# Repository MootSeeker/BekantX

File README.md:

<div align="center">

# BekantX

**An open replacement controller for the IKEA BEKANT standing desk, with its schematic, PCB layout and enclosure designed by an AI (Claude) under human review.**

</div>

---

## What this is

BekantX replaces the button box of an IKEA BEKANT sit/stand desk with a custom controller. It provides memory
positions, limits, obstruction detection, a small OLED display, and an optional Wi-Fi link to Home Assistant
that works locally, without a cloud.

The project is also an **experiment**: how far can an AI model take real hardware design? The schematic changes,
the component placement, the 6-layer PCB layout, the parametric 3D-printed enclosure and the fit checks between
board and case were done by [Claude](https://www.anthropic.com/claude) through
[Claude Code](https://claude.com/claude-code). It worked with scripts and the KiCad and build123d APIs, not
through a GUI. A human set the requirements, made the decisions, reviewed every pull request, and printed and
tested the parts.

> [!NOTE]
> Part of the point is to be honest about the results. Every pull request lists what was verified (ERC, DRC,
> fit check, renders) and what was not. Open findings are tracked in the project notes in
> [`Vault/`](Vault/00%20Index.md).

## Highlights

- **Dual controller, safety first.** An STM32G0B1 owns the LIN bus to the desk, motion and every safety rule.
  An optional ESP32-C3 adds Wi-Fi, MQTT and Home Assistant discovery. The desk keeps working without the ESP,
  and the ESP can never move the desk without the STM32's validation.
- **One 6-layer board.** 129 × 38 mm, one track direction per layer: F.Cu vertical, In1 (+3V3 and VCC area),
  In2 horizontal, In3 vertical, In4 (solid GND), B.Cu horizontal. Routed with Freerouting, tuned by parameter
  sweeps, then finished by scripts: tracks through pad and via centres, only 45° corners, via teardrops, short
  supply stubs to the planes and large GND pours on the outer layers that are cut as little as possible.
- **Parametric enclosure.** Built in [build123d](https://github.com/gumyr/build123d), with every dimension a
  named parameter. The board outline, mounting holes, buttons and display position are exported from the
  enclosure model to the PCB (`CAD/board_interface.json`), and the board STEP is checked against the case for
  collisions.
- **Local smart home.** ESP-IDF C++ firmware with a Wi-Fi captive portal, MQTT, Home Assistant auto discovery
  and a status LED.
- **Reproducible.** Every layout step is a script in [`tools/pcb/`](tools/pcb). The design rules, decisions
  and open points are documented in the vault.

## Gallery

<table>
  <tr>
    <td align="center"><br><sub>Front side: six buttons, OLED connector, status LEDs, title block with QR code</sub></td>
    <td align="center"><br><sub>Back side: input protection and regulators, STM32G0B1, ESP32-C3 with chip antenna, USB-C</sub></td>
  </tr>
  <tr>
    <td align="center"><br><sub>Board, case and lid (render of the CAD models)</sub></td>
    <td align="center"><br><sub>Enclosure r3, printed in PLA (without keypad and board)</sub></td>
  </tr>
</table>

## Architecture

```mermaid
flowchart TB
    desk["IKEA BEKANT motor controller"]
    ha["Home Assistant"]
    subgraph board["BekantX controller board"]
        direction TB
        esp["ESP32-C3 (secondary, optional)<br/>Wi-Fi, MQTT"]
        stm["STM32G0B1 (primary)<br/>LIN, motion, limits, safety, memory"]
        hmi["6 buttons, 1.29 in OLED, LEDs"]
    end
    ha <-- "MQTT + discovery" --> esp
    esp <-- "SPI mailbox, validated by the primary" --> stm
    hmi --- stm
    stm <-- "LIN (TLIN1027)" --> desk
```

| Document | Content |
| --- | --- |
| [Requirements](Docs/description.md) | Goals, functional and safety requirements (SR-001 … SR-007) |
| [Architecture](Docs/architecture.md) | Controller split, responsibilities, state ownership |
| [Inter-controller protocol](Docs/inter-controller-protocol.md) | SPI frames between ESP32-C3 and STM32 |
| [BEKANT LIN protocol](Docs/bekant-lin-protocol.md) | What is known about the desk's LIN bus |
| [Assembly guide](Docs/Montageanleitung.md) | Printing, keypad, display, board, lid and mounting under the desktop (German); English PDF: [BekantX_Assembly_Guide.pdf](Docs/BekantX_Assembly_Guide.pdf) |
| [Bill of materials](Docs/BekantX_Bill_of_Materials.pdf) | 127 board placements (6 not populated) and the parts outside the PCB |
| [Renderings and photos](Docs/bilder/README.md) | Board and enclosure renders, photos of the printed case |
| [`Docs/datasheets/`](Docs/datasheets) | Third-party datasheets (display, ESP32, LMR51610), see [LICENSES](LICENSES/README.md) |

## Hardware at a glance

| Block | Parts |
| --- | --- |
| Primary MCU | STM32G0B1KB (QFN-32) |
| Secondary MCU | ESP32-C3 + W25Q32 flash, Johanson 2450AT18A100 chip antenna |
| Desk interface | 3-pin connector (supply, GND, LIN), TLIN1027 LIN transceiver, fuse, TVS SMBJ33CA, reverse-polarity protection |
| Power | LV2862 buck to 12 V (LIN VSUP), LMR51610 buck to 3.3 V, USB-C supply as an alternative |
| USB | USB-C with ESD protection (USBLC6), TS3USB30 switch: USB goes to the ESP32-C3 or to the STM32 |
| User interface | 6 × 6 mm tactile buttons, 1.29" OLED (CH1115) on a 16-pin FPC, SK6812 status LED, RGB LED |
| Board | 6 layers, 1.6 mm (stackup ASSUMPTION, JLC06161H-2116 pattern, not yet checked with the fab), 0.15 / 0.15 mm rules, ENIG |

> [!WARNING]
> The desk's electrical interface (supply voltage, LIN levels, connector pinout) has **not been measured** on a
> real desk yet. Those parts of the design are marked `ASSUMPTION` and listed in
> [`Vault/Offene Punkte.md`](Vault/Offene%20Punkte.md). Do not connect this board to your desk before checking
> them.

## How the AI-driven design works

All the work happens in [Claude Code](https://claude.com/claude-code) against this repository:

- **Project memory**: [`CLAUDE.md`](CLAUDE.md) holds the rules (guardrails for electronics, mechanics, firmware
  and git). The Obsidian vault [`Vault/`](Vault/00%20Index.md) holds the *why*: decisions, status and open
  points. The vault is written in German.
- **Roles as skills**: architecture, schematic design, component selection, PCB design, mechanical CAD,
  firmware, tests, CI and fab export. Each is a skill in [`.claude/skills/`](.claude/skills).
- **Independent review**: read-only reviewer subagents (schematic, PCB, CAD, code) check every change without
  the author's bias. Their findings go into the pull request unchanged.
- **Hooks**: [`.claude/hooks/`](.claude/hooks) enforce the git rules and run ERC/DRC automatically after every
  edit to a KiCad file.
- **Layout pipeline** (KiCad 10 Python API, `pcbnew`):
  1. placement from the enclosure interface;
  2. Freerouting in two stages (power first, then signals), with parameter sweeps;
  3. a custom A* touch-up router;
  4. plane rework, pad-entry straightening and corner chamfering;
  5. supply stubs to the planes, GND pour stitching, the board outline, and the silkscreen with labels, logo and QR code;
  6. the move to 6 layers with one track direction per layer (fan-out, direction-constrained routing runs), 45°
     chamfers instead of 90° corners, via teardrops.

  Details: [`Vault/Toolchain.md`](Vault/Toolchain.md).
- **Mechanics**: [`CAD/src/bekantx_enclosure.py`](CAD/src/bekantx_enclosure.py) builds the case, lid and keypad,
  and exports STEP + STL. [`CAD/src/check_board_fit.py`](CAD/src/check_board_fit.py) checks the real board STEP
  against the case.

## Repository layout

```
CAD/              enclosure exports (STEP/STL), board STEP, board interface; sources in CAD/src
Docs/             requirements, architecture, protocols, assembly guide, bill of materials (PDF)
  bilder/         renderings and photos
  datasheets/     third-party datasheets
Firmware/
  ESP32C3/        ESP-IDF C++ firmware of the secondary controller
  ST/             STM32CubeMX project of the primary controller (no code yet)
Pcb_Controller/   KiCad 10 project: hierarchical schematic and 6-layer board
tools/pcb/        layout pipeline (placement, routing, touch-up, post-processing)
tools/sch/        scripted schematic edits
tools/docs/       PDF builders (bill of materials, assembly guide)
Vault/            project memory (Obsidian, German)
.claude/          skills, reviewer subagents and hooks for Claude Code
```

## Build and check

```bash
# KiCad 10: electrical and design rule checks, 3D export (Windows paths, see Vault/Toolchain.md)
kicad-cli sch erc --format json -o erc.json Pcb_Controller/BekantX.kicad_sch
kicad-cli pcb drc --schematic-parity --format json -o drc.json Pcb_Controller/BekantX.kicad_pcb
kicad-cli pcb export step --subst-models --user-origin 100x80mm -o CAD/BekantX_PCB.step Pcb_Controller/BekantX.kicad_pcb

# Enclosure (Python 3.13 with build123d) and fit check against the board
python CAD/src/bekantx_enclosure.py
python CAD/src/check_board_fit.py

# PDFs: bill of materials (KiCad's Python) and assembly guide (Python with Pillow); both print with Microsoft Edge
"C:/Program Files/KiCad/10.0/bin/python.exe" tools/docs/bom_pdf.py
python tools/docs/makerworld_pdf.py

# ESP32-C3 firmware (ESP-IDF environment)
cd Firmware/ESP32C3/BekantX && idf.py set-target esp32c3 && idf.py build
```

## Status

| Area | State |
| --- | --- |
| Requirements and architecture | done, see `Docs/` |
| Schematic | done; ERC 0 errors (28 old warnings) |
| PCB layout (6 layers) | done and reviewed in KiCad; DRC 0 errors, 0 unconnected, schematic parity OK; not yet manufactured |
| Enclosure r3 | printed (PLA); case and lid fit; fit check against the 6-layer board passes in CAD; final print in PETG pending |
| Bill of materials | 127 placements, 121 to populate; no supplier part numbers yet, J10 and Y1 without MPN |
| Assembly guide | written (German and English PDF); not yet tried with a populated board |
| ESP32-C3 firmware | Wi-Fi provisioning, MQTT, Home Assistant discovery, status LED; developed on an ESP32-S2-Saola board until the controller board exists |
| STM32 firmware | not started (CubeMX pin configuration only) |
| Desk interface | **unverified**: to be measured on a real BEKANT |

The next steps are measuring the desk interface, ordering the first boards, writing the STM32 firmware with the
LIN and motion logic, and the inter-controller SPI link. The full list is in
[`Vault/Offene Punkte.md`](Vault/Offene%20Punkte.md).

## Safety and disclaimer

A standing desk is a heavy, motorised machine. BekantX is a hobby project without any certification. Anything
you build from it is at your own risk. Collision detection is heuristic and is no substitute for paying
attention.
"IKEA" and "BEKANT" are trademarks of Inter IKEA Systems B.V. This project is not affiliated with or endorsed
by IKEA.

## License

| Part | License |
| --- | --- |
| Hardware (`Pcb_Controller/`, `CAD/`) | [CERN-OHL-S-2.0](LICENSE) |
| Software (`Firmware/`, `tools/`, `CAD/src/`, `.claude/`) | [GPL-3.0-or-later](LICENSES/GPL-3.0-or-later.txt) |
| Documentation (`Docs/`, `Vault/`, this README) | [CC-BY-SA-4.0](LICENSES/CC-BY-SA-4.0.txt) |

Details and exceptions (third-party datasheets) are in [`LICENSES/README.md`](LICENSES/README.md).

## Acknowledgements

- [LYFT mk2](https://github.com/mgkoenig/lyft_mk2) by mgkoenig: the idea of a LIN controller plus an ESP for
  the BEKANT.
- [KiCad](https://www.kicad.org/), [Freerouting](https://github.com/freerouting/freerouting),
  [build123d](https://github.com/gumyr/build123d) and [ESP-IDF](https://github.com/espressif/esp-idf).
- Designed with [Claude Code](https://claude.com/claude-code) by Anthropic, reviewed and built by
  [MootSeeker](https://github.com/MootSeeker).

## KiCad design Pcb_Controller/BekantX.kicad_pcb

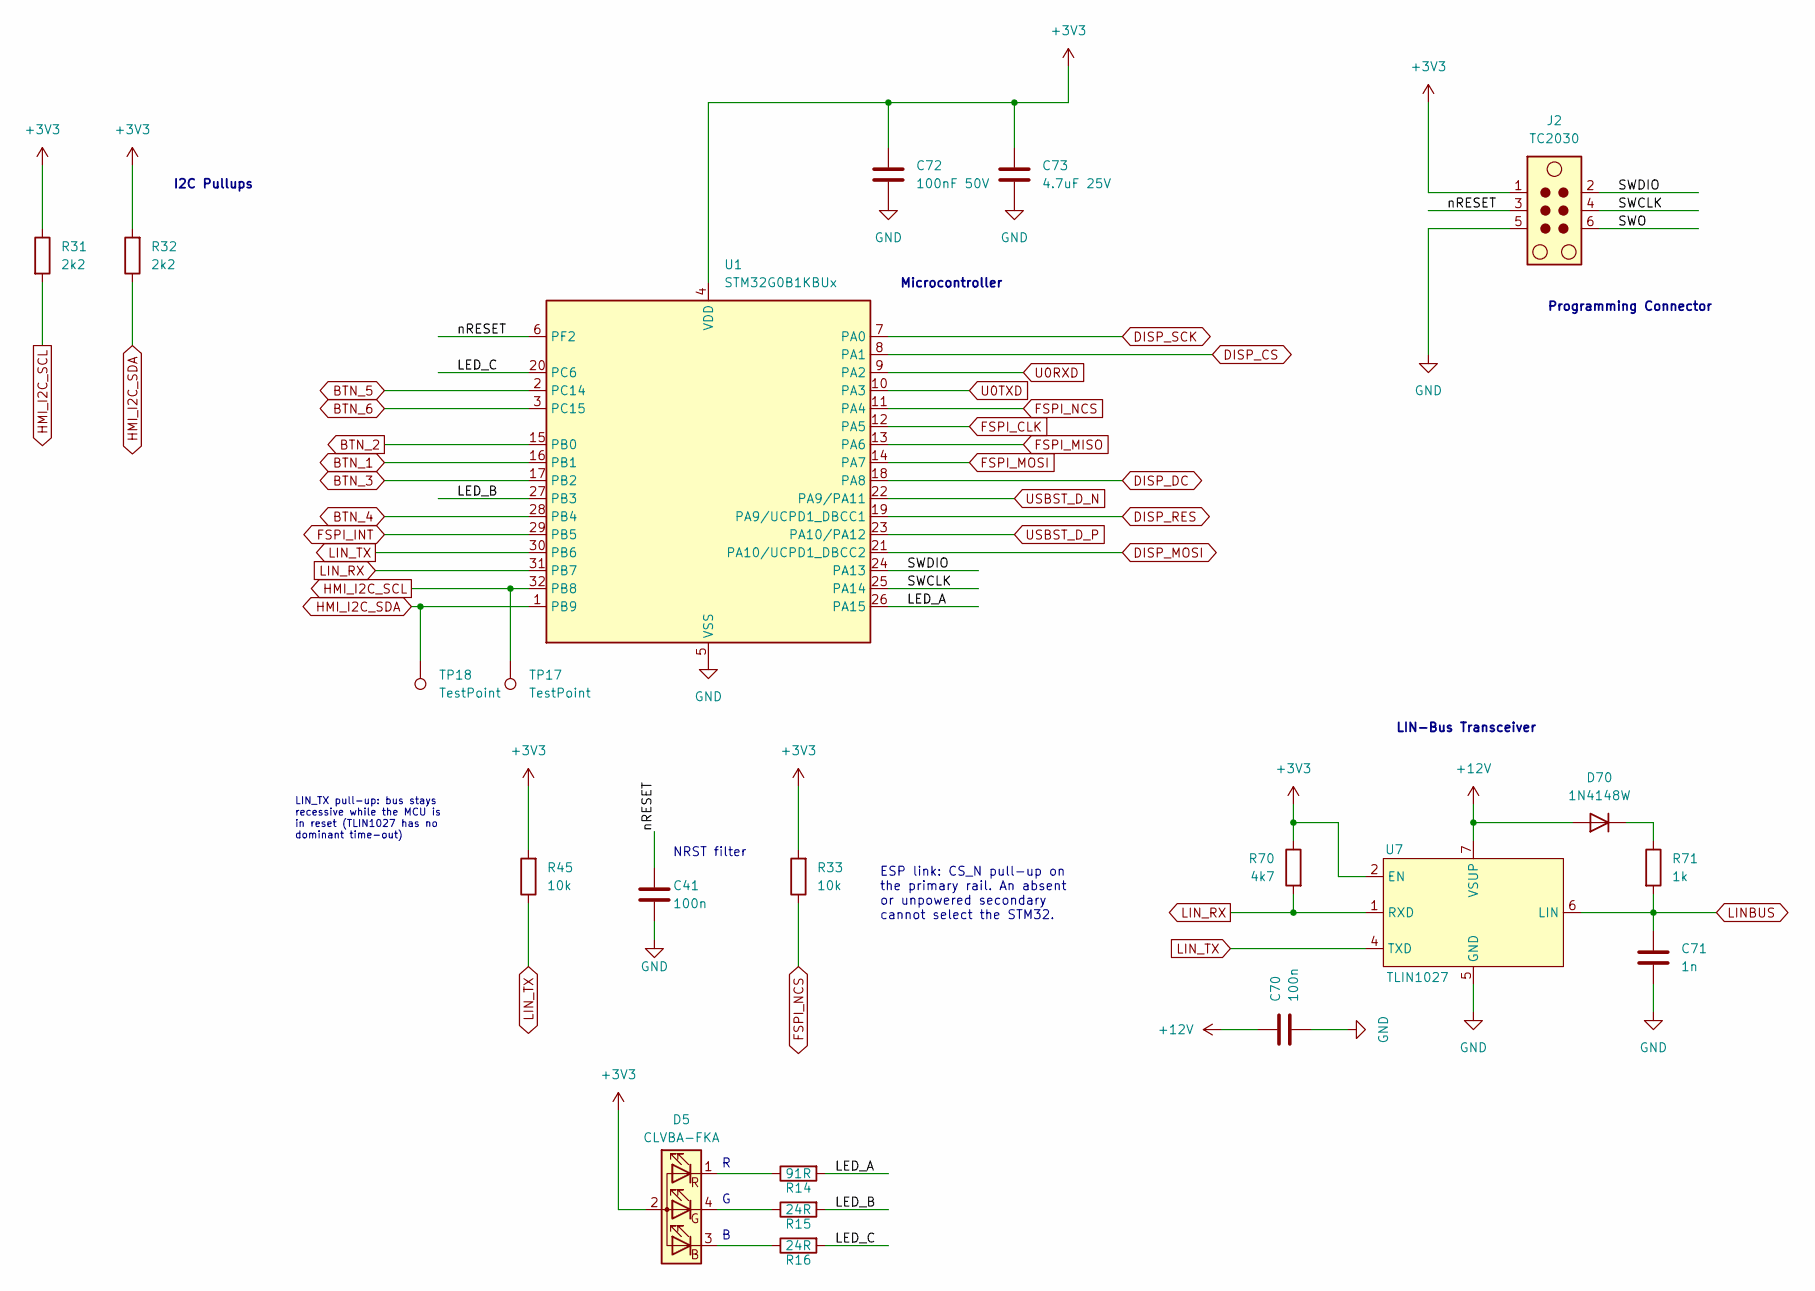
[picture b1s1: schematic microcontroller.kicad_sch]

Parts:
C41, C70: 100n; C_0805_2012Metric; MPN CL21B104KBCNNNC
C71: 1n; C_0805_2012Metric; MPN CL21B102KBANNNC
C72: 100nF 50V; C_0805_2012Metric; MPN CL21B104KBCNNNC
C73: 4.7uF 25V; C_0805_2012Metric; MPN CL21A475KAQNNNE
D5: CLVBA-FKA; LED_Cree-PLCC4_3.2x2.8mm_CCW; MPN CLVBA-FKA-CAEDH8BBB7A363
D70: 1N4148W; D_SOD-123; MPN 1N4148W-7-F
J2: TC2030; Tag-Connect_TC2030-IDC-NL_2x03_P1.27mm_Vertical
R14: 91R; R_0805_2012Metric; MPN RC0805FR-0791RL
R15, R16: 24R; R_0805_2012Metric; MPN RC0805FR-0724RL
R31, R32: 2k2; R_0805_2012Metric; MPN RC0805FR-072K2L
R33, R45: 10k; R_0805_2012Metric; MPN RC0805FR-0710KL
R70: 4k7; R_0805_2012Metric; MPN RC0805FR-074K7L
R71: 1k; R_1206_3216Metric; MPN RC1206FR-071KL
TP17, TP18: TestPoint; TestPoint_Pad_D1.0mm
U1: STM32G0B1KBUx; QFN-32-1EP_5x5mm_P0.5mm_EP3.45x3.45mm; MPN STM32G0B1KBU6
U7: TLIN1027; SOIC-8_3.9x4.9mm_P1.27mm; MPN TLIN1027DRQ1

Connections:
+3V3: C72.1, C73.1, D5.2 (A), J2.1, R31.1, R32.2, R33.2, R45.2, R70.1, U1.4 (VDD), U7.2 (EN); also elsewhere on the board
+12V: C70.2, D70.2 (A), U7.7 (VSUP); also elsewhere on the board
/Microcontroller/LED_A: R14.2, U1.26 (PA15)
/Microcontroller/LED_B: R15.2, U1.27 (PB3)
/Microcontroller/LED_C: R16.2, U1.20 (PC6)
/Microcontroller/SWCLK: J2.4, U1.25 (PA14)
/Microcontroller/SWDIO: J2.2, U1.24 (PA13)
/Microcontroller/SWO: J2.6
/Microcontroller/nRESET: C41.1, J2.3, U1.6 (PF2)
BTN_1: U1.16 (PB1); also elsewhere on the board
BTN_2: U1.15 (PB0); also elsewhere on the board
BTN_3: U1.17 (PB2); also elsewhere on the board
BTN_4: U1.28 (PB4); also elsewhere on the board
BTN_5: U1.2 (PC14); also elsewhere on the board
BTN_6: U1.3 (PC15); also elsewhere on the board
DISP_CS: U1.8 (PA1); also elsewhere on the board
DISP_DC: U1.18 (PA8); also elsewhere on the board
DISP_MOSI: U1.21 (PA10/UCPD1_DBCC2); also elsewhere on the board
DISP_RES: U1.19 (PA9/UCPD1_DBCC1); also elsewhere on the board
DISP_SCK: U1.7 (PA0); also elsewhere on the board
FSPI_CLK: U1.12 (PA5); also elsewhere on the board
FSPI_INT: U1.29 (PB5); also elsewhere on the board
FSPI_MISO: U1.13 (PA6); also elsewhere on the board
FSPI_MOSI: U1.14 (PA7); also elsewhere on the board
FSPI_NCS: R33.1, U1.11 (PA4); also elsewhere on the board
GND: C41.2, C70.1, C71.1, C72.2, C73.2, J2.5, U1.5 (VSS), U1.33 (VSS), U7.5 (GND); also elsewhere on the board
HMI_I2C_SCL: R31.2, TP17.1 (1_1), U1.32 (PB8); also elsewhere on the board
HMI_I2C_SDA: R32.1, TP18.1 (1_1), U1.1 (PB9); also elsewhere on the board
LINBUS: C71.2, R71.2, U7.6 (LIN); also elsewhere on the board
LIN_RX: R70.2, U1.31 (PB7), U7.1 (RXD)
LIN_TX: R45.1, U1.30 (PB6), U7.4 (TXD)
unnamed: D5.3 (BK), R16.1
unnamed: D5.4 (GK), R15.1
unnamed: D5.1 (RK), R14.1
unnamed: D70.1 (K), R71.1
U0RXD: U1.9 (PA2); also elsewhere on the board
U0TXD: U1.10 (PA3); also elsewhere on the board
USBST_D_N: U1.22 (PA9/PA11); also elsewhere on the board
USBST_D_P: U1.23 (PA10/PA12); also elsewhere on the board

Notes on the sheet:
Microcontroller
LIN-Bus Transceiver
I2C Pullups
Programming Connector
ESP link: CS_N pull-up on the primary rail. An absent or unpowered secondary cannot select the STM32.
NRST filter
LIN_TX pull-up: bus stays recessive while the MCU is in reset (TLIN1027 has no dominant time-out)

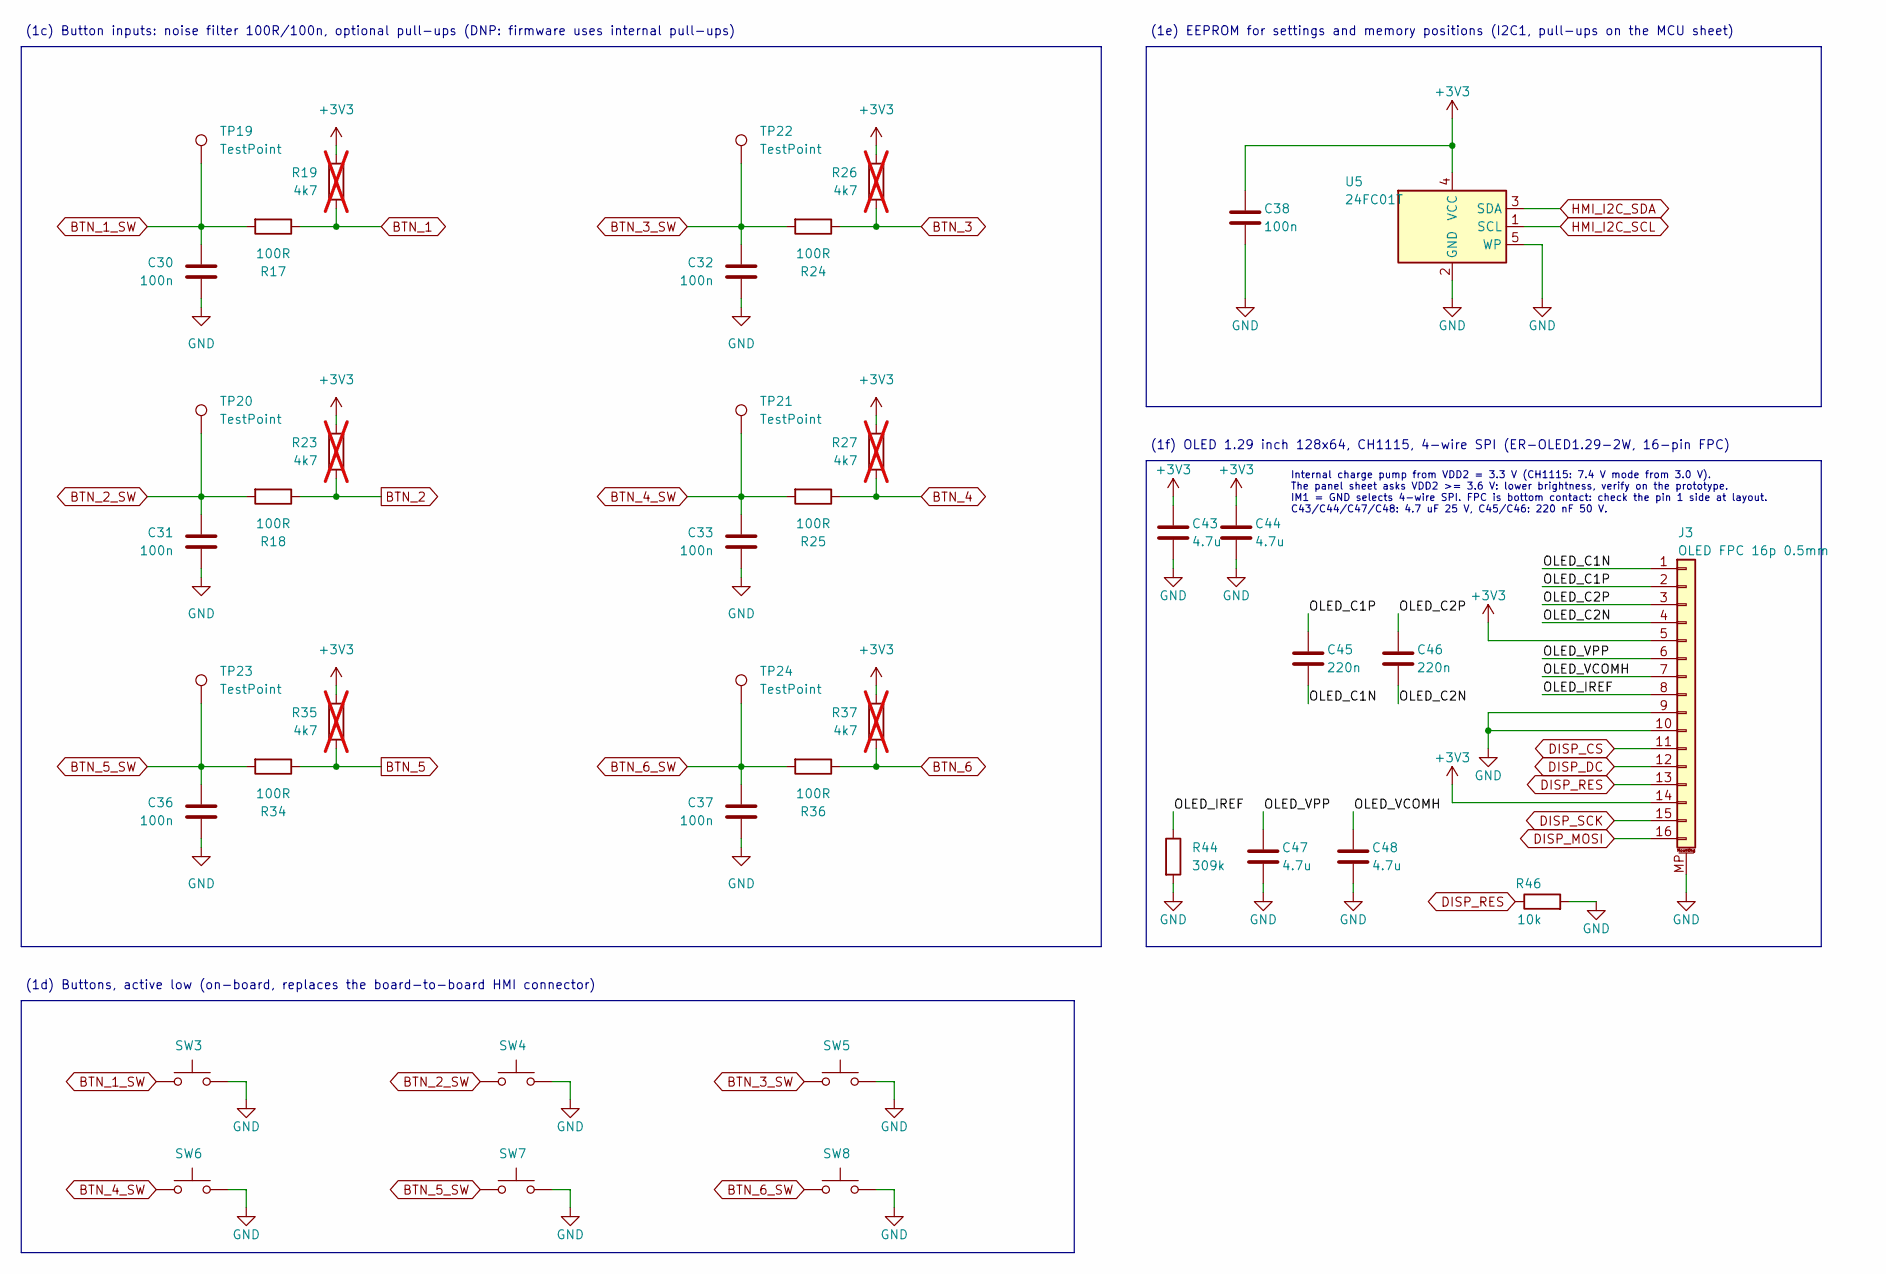
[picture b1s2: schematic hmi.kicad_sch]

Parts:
C30, C31, C32, C33, C36, C37, C38: 100n; C_0805_2012Metric; MPN CL21B104KBCNNNC
C43, C44, C47, C48: 4.7u; C_0805_2012Metric; MPN CL21A475KAQNNNE
C45, C46: 220n; C_0805_2012Metric; MPN CL21B224KBFNNNE
J3: OLED FPC 16p 0.5mm; Hirose_FH12-16S-0.5SH_1x16-1MP_P0.50mm_Horizontal; MPN FH12-16S-0.5SH(55)
R17, R18, R24, R25, R34, R36: 100R; R_0805_2012Metric; MPN RC0805FR-07100RL
R19, R23, R26, R27, R35, R37: 4k7; R_0805_2012Metric; MPN RC0805FR-074K7L; not fitted
R44: 309k; R_0805_2012Metric; MPN RC0805FR-07309KL
R46: 10k; R_0805_2012Metric; MPN RC0805FR-0710KL
SW3, SW4, SW5, SW6, SW7, SW8: B3F-1000; SW_PUSH_6mm; MPN B3F-1000
TP19, TP20, TP21, TP22, TP23, TP24: TestPoint; TestPoint_Pad_D1.0mm
U5: 24FC01T; SOT-23-5; MPN 24FC01T-I/OT

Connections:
+3V3: C38.1, C43.1, C44.1, J3.5, J3.14, R19.2, R23.2, R26.2, R27.2, R35.2, R37.2, U5.4 (VCC); also elsewhere on the board
/HMI/OLED_C1N: C45.2, J3.1
/HMI/OLED_C1P: C45.1, J3.2
/HMI/OLED_C2N: C46.2, J3.4
/HMI/OLED_C2P: C46.1, J3.3
/HMI/OLED_IREF: J3.8, R44.1
/HMI/OLED_VCOMH: C48.1, J3.7
/HMI/OLED_VPP: C47.1, J3.6
BTN_1: R17.1, R19.1; also elsewhere on the board
BTN_1_SW: C30.2, R17.2, SW3.1, TP19.1 (1_1)
BTN_2: R18.1, R23.1; also elsewhere on the board
BTN_2_SW: C31.2, R18.2, SW4.1, TP20.1 (1_1)
BTN_3: R24.1, R26.1; also elsewhere on the board
BTN_3_SW: C32.2, R24.2, SW5.1, TP22.1 (1_1)
BTN_4: R25.1, R27.1; also elsewhere on the board
BTN_4_SW: C33.2, R25.2, SW6.1, TP21.1 (1_1)
BTN_5: R34.1, R35.1; also elsewhere on the board
BTN_5_SW: C36.2, R34.2, SW7.1, TP23.1 (1_1)
BTN_6: R36.1, R37.1; also elsewhere on the board
BTN_6_SW: C37.2, R36.2, SW8.1, TP24.1 (1_1)
DISP_CS: J3.11; also elsewhere on the board
DISP_DC: J3.12; also elsewhere on the board
DISP_MOSI: J3.16; also elsewhere on the board
DISP_RES: J3.13, R46.1; also elsewhere on the board
DISP_SCK: J3.15; also elsewhere on the board
GND: C30.1, C31.1, C32.1, C33.1, C36.1, C37.1, C38.2, C43.2, C44.2, C47.2, C48.2, J3.9, J3.10, J3.MP (MountPin), R44.2, R46.2, SW3.2, SW4.2, SW5.2, SW6.2, SW7.2, SW8.2, U5.2 (GND), U5.5 (WP); also elsewhere on the board
HMI_I2C_SCL: U5.1 (SCL); also elsewhere on the board
HMI_I2C_SDA: U5.3 (SDA); also elsewhere on the board

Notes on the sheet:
(1c) Button inputs: noise filter 100R/100n, optional pull-ups (DNP: firmware uses internal pull-ups)
(1d) Buttons, active low (on-board, replaces the board-to-board HMI connector)
(1e) EEPROM for settings and memory positions (I2C1, pull-ups on the MCU sheet)
(1f) OLED 1.29 inch 128x64, CH1115, 4-wire SPI (ER-OLED1.29-2W, 16-pin FPC)
Internal charge pump from VDD2 = 3.3 V (CH1115: 7.4 V mode from 3.0 V). The panel sheet asks VDD2 >= 3.6 V: lower brightness, verify on the prototype. IM1 = GND selects 4-wire SPI. FPC is bottom contact: check the pin 1 side at layout. C43/C44/C47/C48: 4.7 uF 25 V, C45/C46: 220 nF 50 V.

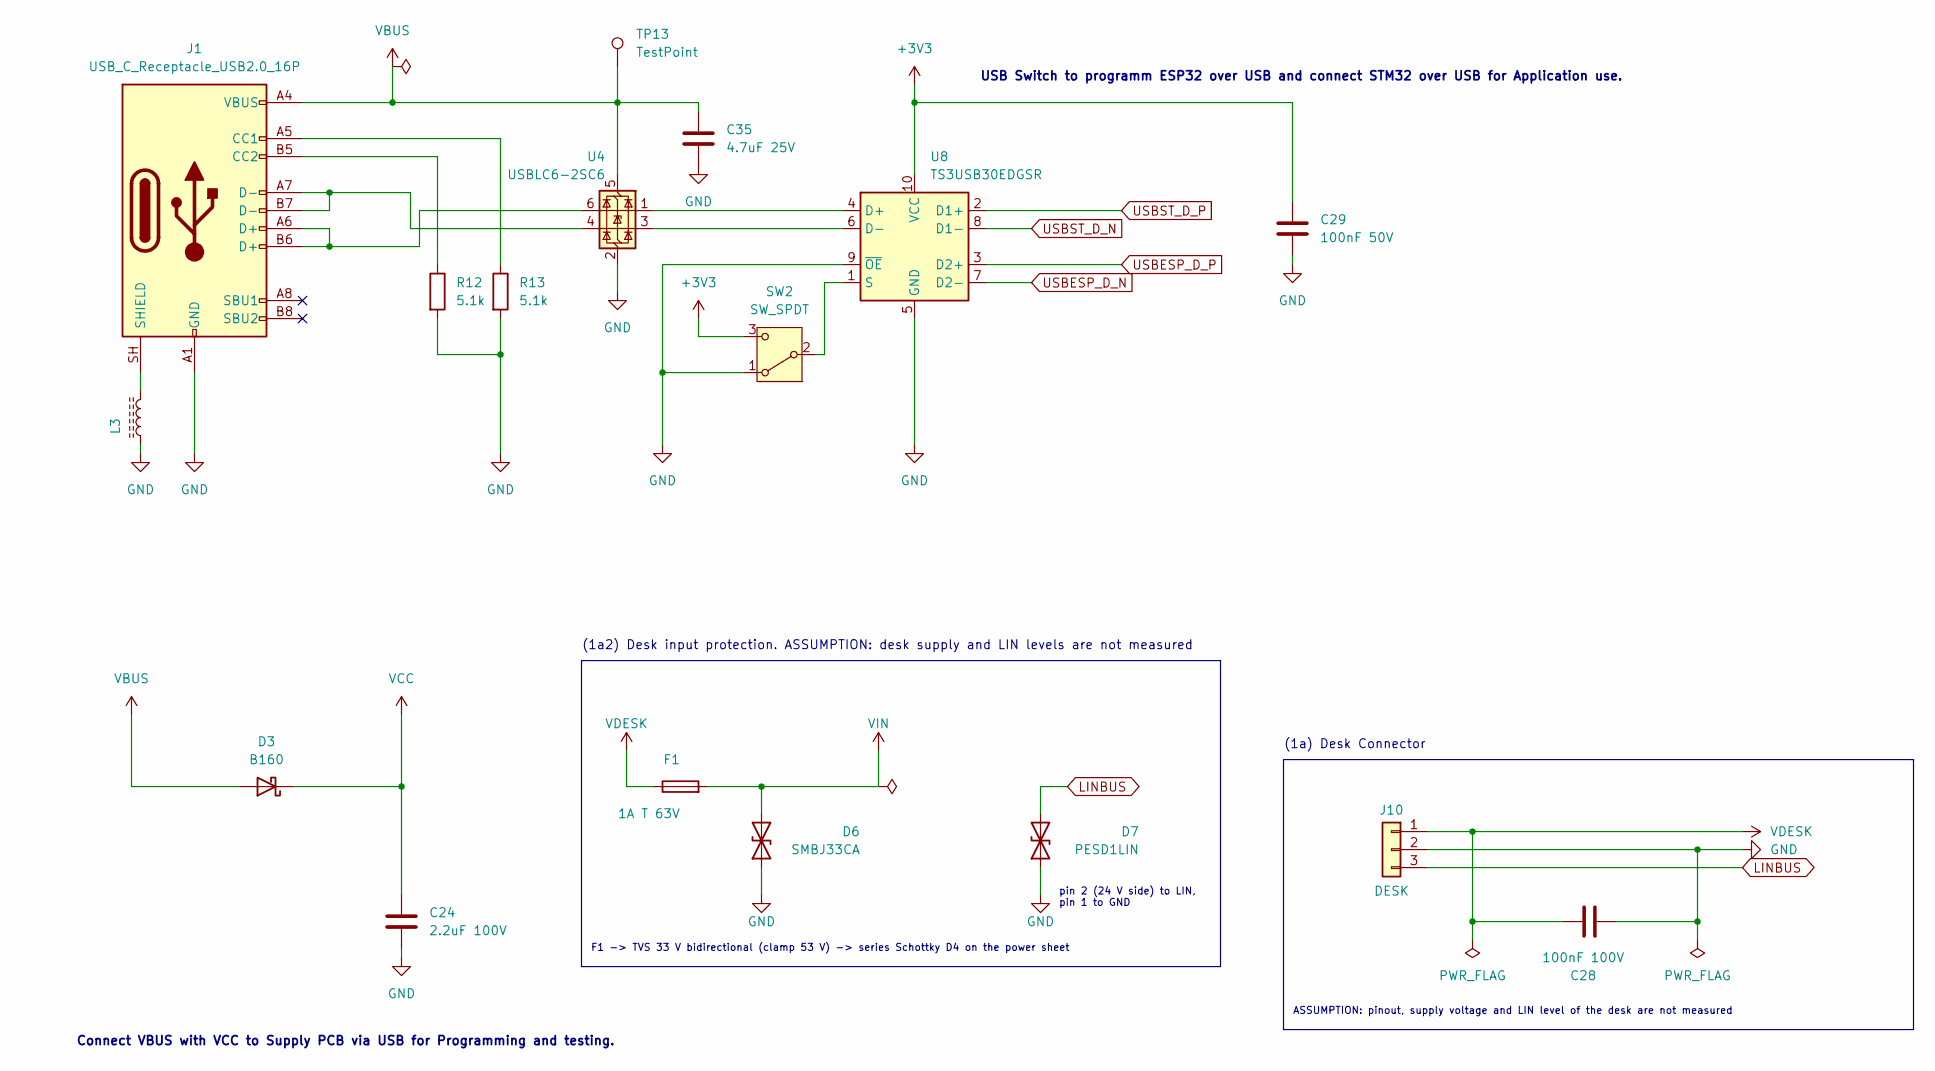
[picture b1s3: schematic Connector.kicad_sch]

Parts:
C24: 2.2uF 100V; C_1206_3216Metric; MPN C3216X7S2A225K160AB
C28: 100nF 100V; C_0805_2012Metric; MPN CL21B104KCFNNNE
C29: 100nF 50V; C_0805_2012Metric; MPN CL21B104KBCNNNC
C35: 4.7uF 25V; C_0805_2012Metric; MPN CL21A475KAQNNNE
D3: B160; D_SMA; MPN B160-13-F
D6: SMBJ33CA; D_SMB; MPN SMBJ33CA
D7: PESD1LIN; D_SOD-323; MPN PESD1LIN,115
F1: 1A T 63V; Fuse_1206_3216Metric; MPN 0468001.NR
J1: USB_C_Receptacle_USB2.0_16P; USB_C_Receptacle_HRO_TYPE-C-31-M-12; MPN TYPE-C-31-M-12
J10: DESK; PinHeader_1x03_P2.54mm_Horizontal
L3: 220R@100MHz; L_0805_2012Metric; MPN BLM21PG221SN1D
R12, R13: 5.1k; R_0805_2012Metric; MPN RC0805FR-075K1L
SW2: SW_SPDT; SW_SPDT_CK_JS102011SAQN; MPN JS102011SAQN
TP13: TestPoint; TestPoint_Pad_D1.0mm
U4: USBLC6-2SC6; SOT-23-6; MPN USBLC6-2SC6
U8: TS3USB30EDGSR; TSSOP-10_3x3mm_P0.5mm; MPN TS3USB30EDGSR

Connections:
+3V3: C29.1, SW2.3 (C), U8.10 (VCC); also elsewhere on the board
GND: C24.2, C28.2, C29.2, C35.2, D6.1 (A1), D7.1 (A1), J1.A1 (GND), J1.A12 (GND), J1.B1 (GND), J1.B12 (GND), J10.2, L3.2, R12.2, R13.2, SW2.1 (A), U4.2 (GND), U8.5 (GND), U8.9 (~OE); also elsewhere on the board
LINBUS: D7.2 (A2), J10.3; also elsewhere on the board
unnamed: J1.A5 (CC1), R13.1
unnamed: J1.B5 (CC2), R12.1
unnamed: J1.A6 (D+), J1.B6 (D+), U4.6 (I/O1)
unnamed: J1.A7 (D-), J1.B7 (D-), U4.4 (I/O2)
unnamed: J1.SH (SHIELD), L3.1
unnamed: SW2.2 (B), U8.1 (S)
unnamed: U4.1 (I/O1), U8.4 (D+)
unnamed: U4.3 (I/O2), U8.6 (D-)
USBESP_D_N: U8.7 (D2-); also elsewhere on the board
USBESP_D_P: U8.3 (D2+); also elsewhere on the board
USBST_D_N: U8.8 (D1-); also elsewhere on the board
USBST_D_P: U8.2 (D1+); also elsewhere on the board
VBUS: C35.1, D3.2 (A), J1.A4 (VBUS), J1.A9 (VBUS), J1.B4 (VBUS), J1.B9 (VBUS), TP13.1 (1_1), U4.5 (VBUS)
VCC: C24.1, D3.1 (K); also elsewhere on the board
VDESK: C28.1, F1.1, J10.1
VIN: D6.2 (A2), F1.2; also elsewhere on the board

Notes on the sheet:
(1a) Desk Connector
USB Switch to programm ESP32 over USB and connect STM32 over USB for Application use.
Connect VBUS with VCC to Supply PCB via USB for Programming and testing.
(1a2) Desk input protection. ASSUMPTION: desk supply and LIN levels are not measured
pin 2 (24 V side) to LIN, pin 1 to GND
F1 -> TVS 33 V bidirectional (clamp 53 V) -> series Schottky D4 on the power sheet
ASSUMPTION: pinout, supply voltage and LIN level of the desk are not measured

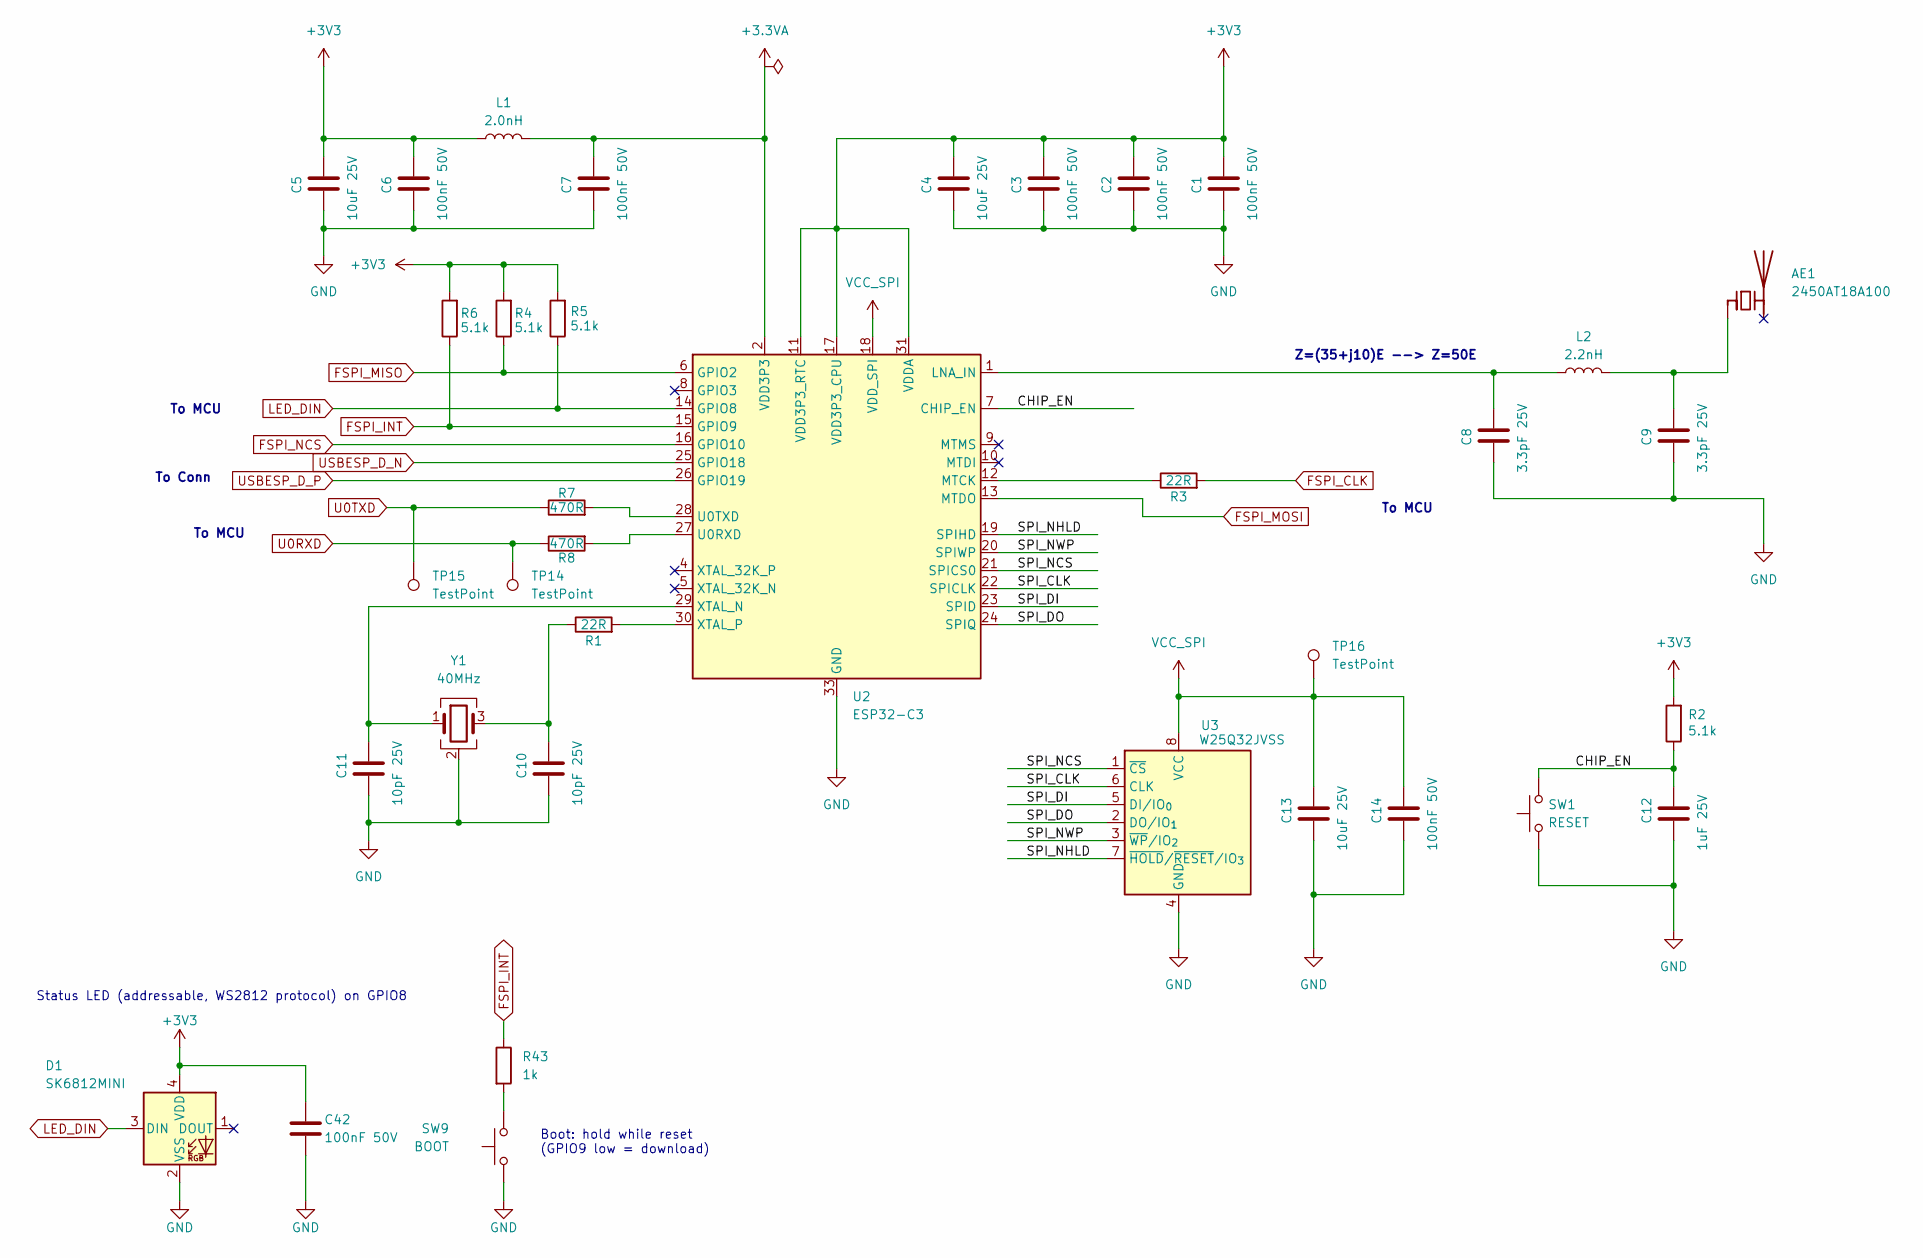
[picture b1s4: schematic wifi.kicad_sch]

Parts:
AE1: 2450AT18A100; Johanson_2450AT18x100; MPN 2450AT18A100E
C1, C2, C3, C6, C7, C14, C42: 100nF 50V; C_0805_2012Metric; MPN CL21B104KBCNNNC
C4, C5, C13: 10uF 25V; C_0805_2012Metric; MPN CL21A106KAYNNNE
C8, C9: 3.3pF 25V; C_0402_1005Metric; MPN GRM1555C1H3R3CA01D
C10, C11: 10pF 25V; C_0805_2012Metric; MPN CL21C100JBANNNC
C12: 1uF 25V; C_0805_2012Metric; MPN CL21B105KAFNNNE
D1: SK6812MINI; LED_SK6812MINI_PLCC4_3.5x3.5mm_P1.75mm; MPN SK6812MINI
L1: 2.0nH; L_0402_1005Metric; MPN LQP15MN2N0B02D
L2: 2.2nH; L_0402_1005Metric; MPN LQP15MN2N2B02D
R1, R3: 22R; R_0805_2012Metric; MPN RC0805FR-0722RL
R2, R4, R5, R6: 5.1k; R_0805_2012Metric; MPN RC0805FR-075K1L
R7, R8: 470R; R_0805_2012Metric; MPN RC0805FR-07470RL
R43: 1k; R_0805_2012Metric; MPN RC0805FR-071KL
SW1: RESET; SW_SPST_PTS810; MPN PTS810 SJM 250 SMTR LFS
SW9: BOOT; SW_SPST_PTS810; MPN PTS810 SJM 250 SMTR LFS
TP14, TP15, TP16: TestPoint; TestPoint_Pad_D1.0mm
U2: ESP32-C3; QFN-32-1EP_5x5mm_P0.5mm_EP3.7x3.7mm; MPN ESP32-C3
U3: W25Q32JVSS; SOIC-8_5.3x5.3mm_P1.27mm; MPN W25Q32JVSSIQ
Y1: 40MHz; Crystal_SMD_3225-4Pin_3.2x2.5mm

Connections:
+3.3VA: C7.1, L1.2, U2.2 (VDD3P3), U2.3 (VDD3P3)
+3V3: C1.1, C2.1, C3.1, C4.1, C5.1, C6.1, C42.1, D1.4 (VDD), L1.1, R2.2, R4.2, R5.2, R6.2, U2.11 (VDD3P3_RTC), U2.17 (VDD3P3_CPU), U2.31 (VDDA), U2.32 (VDDA); also elsewhere on the board
/WiFi/CHIP_EN: C12.1, R2.1, SW1.2, U2.7 (CHIP_EN)
/WiFi/SPI_CLK: U2.22 (SPICLK), U3.6 (CLK)
/WiFi/SPI_DI: U2.23 (SPID), U3.5 (DI/IO_{0})
/WiFi/SPI_DO: U2.24 (SPIQ), U3.2 (DO/IO_{1})
/WiFi/SPI_NCS: U2.21 (SPICS0), U3.1 (~CS)
/WiFi/SPI_NHLD: U2.19 (SPIHD), U3.7 (~HOLD/~RESET/IO_{3})
/WiFi/SPI_NWP: U2.20 (SPIWP), U3.3 (~WP/IO_{2})
FSPI_CLK: R3.2; also elsewhere on the board
FSPI_INT: R6.1, R43.1, U2.15 (GPIO9); also elsewhere on the board
FSPI_MISO: R4.1, U2.6 (GPIO2); also elsewhere on the board
FSPI_MOSI: U2.13 (MTDO); also elsewhere on the board
FSPI_NCS: U2.16 (GPIO10); also elsewhere on the board
GND: C1.2, C2.2, C3.2, C4.2, C5.2, C6.2, C7.2, C8.2, C9.2, C10.2, C11.2, C12.2, C13.2, C14.2, C42.2, D1.2 (VSS), SW1.1, SW9.1, U2.33 (GND), U3.4 (GND), Y1.2 (G), Y1.4 (G); also elsewhere on the board
LED_DIN: D1.3 (DIN), R5.1, U2.14 (GPIO8)
unnamed: AE1.1 (FEED_1), C9.1, L2.2
unnamed: C10.1, R1.1, Y1.3
unnamed: R43.2, SW9.2
unnamed: C8.1, L2.1, U2.1 (LNA_IN)
unnamed: R3.1, U2.12 (MTCK)
unnamed: R8.2, U2.27 (U0RXD)
unnamed: R7.2, U2.28 (U0TXD)
unnamed: C11.1, U2.29 (XTAL_N), Y1.1
unnamed: R1.2, U2.30 (XTAL_P)
U0RXD: R8.1, TP14.1 (1_1); also elsewhere on the board
U0TXD: R7.1, TP15.1 (1_1); also elsewhere on the board
USBESP_D_N: U2.25 (GPIO18); also elsewhere on the board
USBESP_D_P: U2.26 (GPIO19); also elsewhere on the board
VCC_SPI: C13.1, C14.1, TP16.1 (1_1), U2.18 (VDD_SPI), U3.8 (VCC)

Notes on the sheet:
To MCU
Z=(35+j10)E --> Z=50E
To Conn
Status LED (addressable, WS2812 protocol) on GPIO8
Boot: hold while reset (GPIO9 low = download)

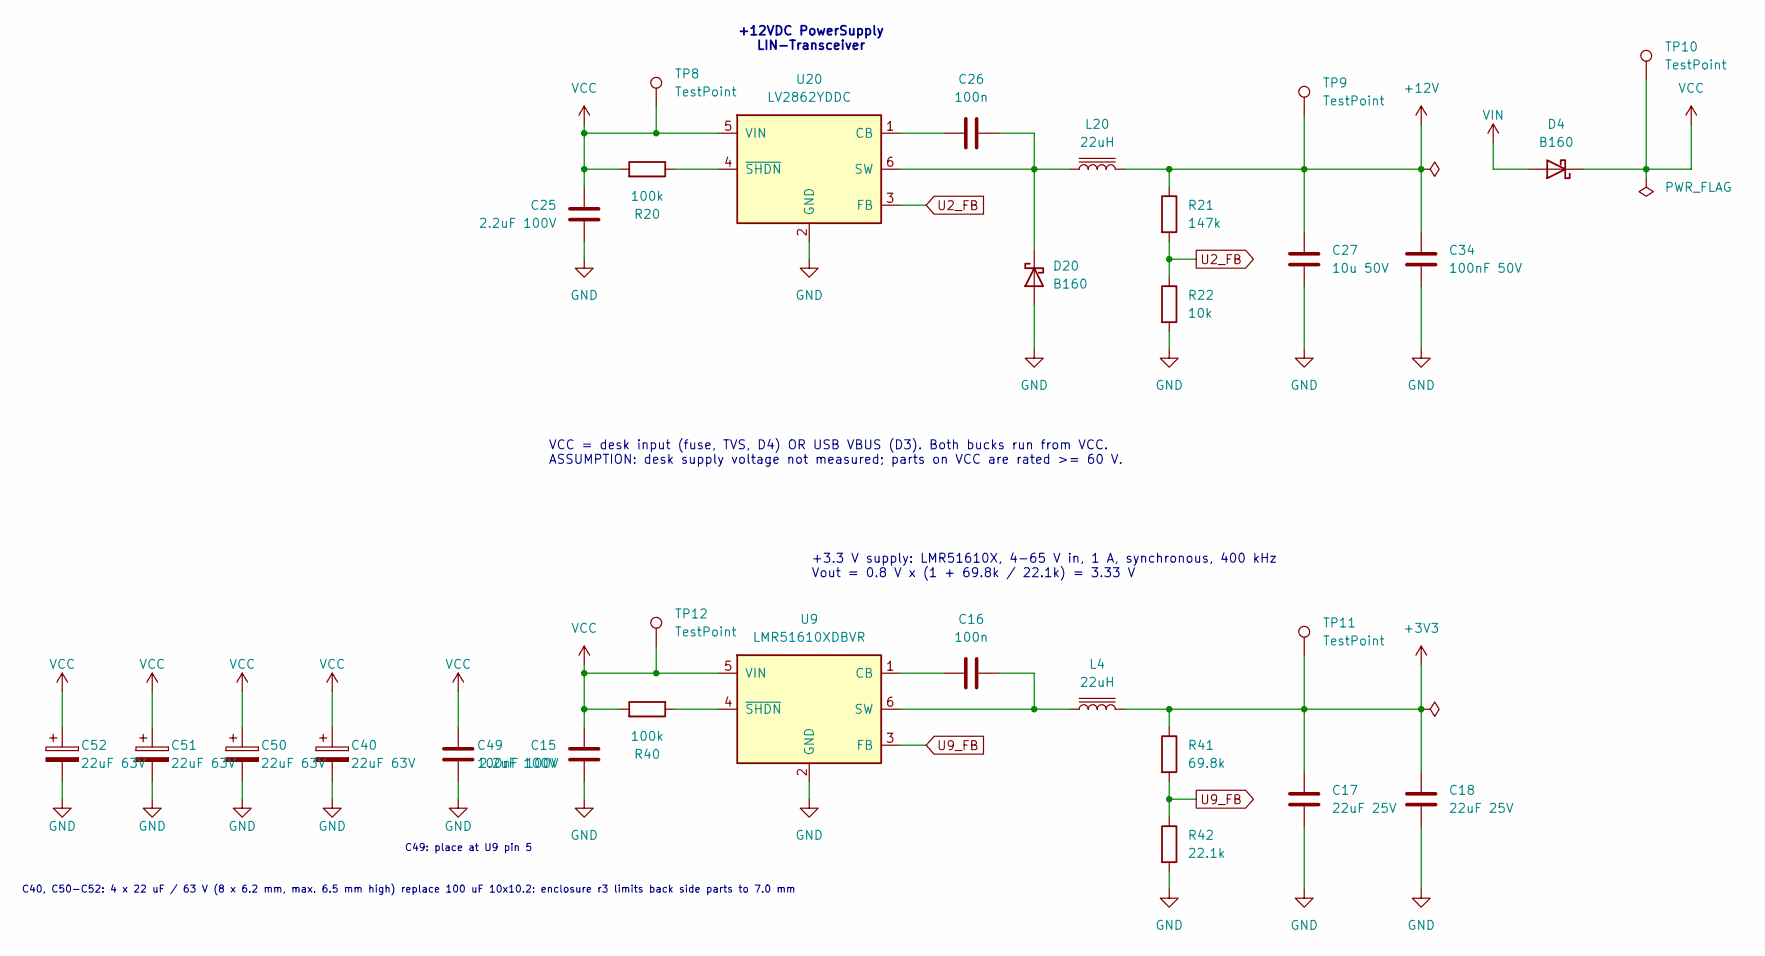
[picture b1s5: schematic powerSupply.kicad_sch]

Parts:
C15, C25: 2.2uF 100V; C_1206_3216Metric; MPN C3216X7S2A225K160AB
C16, C26: 100n; C_0805_2012Metric; MPN CL21B104KBCNNNC
C17, C18: 22uF 25V; C_1206_3216Metric; MPN CL31A226KAHNNNE
C27: 10u 50V; C_1206_3216Metric; MPN CL31A106KBHNNNE
C34: 100nF 50V; C_1206_3216Metric; MPN CL31B104KBCNNNC
C40, C50, C51, C52: 22uF 63V; CP_Elec_8x6.2; MPN EEE-FK1J220P
C49: 100nF 100V; C_0805_2012Metric; MPN CL21B104KCFNNNE
D4, D20: B160; D_SMA; MPN B160-13-F
L4, L20: 22uH; L_Bourns_SRN6045TA; MPN SRN6045TA-220M
R20, R40: 100k; R_0805_2012Metric; MPN RC0805FR-07100KL
R21: 147k; R_0805_2012Metric; MPN RC0805FR-07147KL
R22: 10k; R_0805_2012Metric; MPN RC0805FR-0710KL
R41: 69.8k; R_0805_2012Metric; MPN RC0805FR-0769K8L
R42: 22.1k; R_0805_2012Metric; MPN RC0805FR-0722K1L
TP8, TP9, TP10, TP11, TP12: TestPoint; TestPoint_Pad_D1.0mm
U9: LMR51610XDBVR; SOT-23-6; MPN LMR51610XDBVR
U20: LV2862YDDC; SOT-23-6; MPN LV2862YDDCR

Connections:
+3V3: C17.1, C18.1, L4.2, R41.1, TP11.1 (1_1); also elsewhere on the board
+12V: C27.1, C34.1, L20.2, R21.1, TP9.1 (1_1); also elsewhere on the board
GND: C15.2, C17.2, C18.2, C25.2, C27.2, C34.2, C40.2, C49.2, C50.2, C51.2, C52.2, D20.2 (A), R22.2, R42.2, U9.2 (GND), U20.2 (GND); also elsewhere on the board
unnamed: C26.2, D20.1 (K), L20.1, U20.6 (SW)
unnamed: C16.1, U9.1 (CB)
unnamed: C16.2, L4.1, U9.6 (SW)
unnamed: R40.1, U9.4 (~SHDN)
unnamed: C26.1, U20.1 (CB)
unnamed: R20.1, U20.4 (~SHDN)
U2_FB: R21.2, R22.1, U20.3 (FB)
U9_FB: R41.2, R42.1, U9.3 (FB)
VCC: C15.1, C25.1, C40.1, C49.1, C50.1, C51.1, C52.1, D4.1 (K), R20.2, R40.2, TP8.1 (1_1), TP10.1 (1_1), TP12.1 (1_1), U9.5 (VIN), U20.5 (VIN); also elsewhere on the board
VIN: D4.2 (A); also elsewhere on the board

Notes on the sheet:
+12VDC PowerSupply LIN-Transceiver
+3.3 V supply: LMR51610X, 4-65 V in, 1 A, synchronous, 400 kHz Vout = 0.8 V x (1 + 69.8k / 22.1k) = 3.33 V
VCC = desk input (fuse, TVS, D4) OR USB VBUS (D3). Both bucks run from VCC. ASSUMPTION: desk supply voltage not measured; parts on VCC are rated >= 60 V.
C49: place at U9 pin 5
C40, C50-C52: 4 x 22 uF / 63 V (8 x 6.2 mm, max. 6.5 mm high) replace 100 uF 10x10.2: enclosure r3 limits back side parts to 7.0 mm

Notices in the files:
README.md:
Hardware: CERN-OHL-S-2.0
Software: GPL-3.0
Docs: CC BY-SA 4.0
